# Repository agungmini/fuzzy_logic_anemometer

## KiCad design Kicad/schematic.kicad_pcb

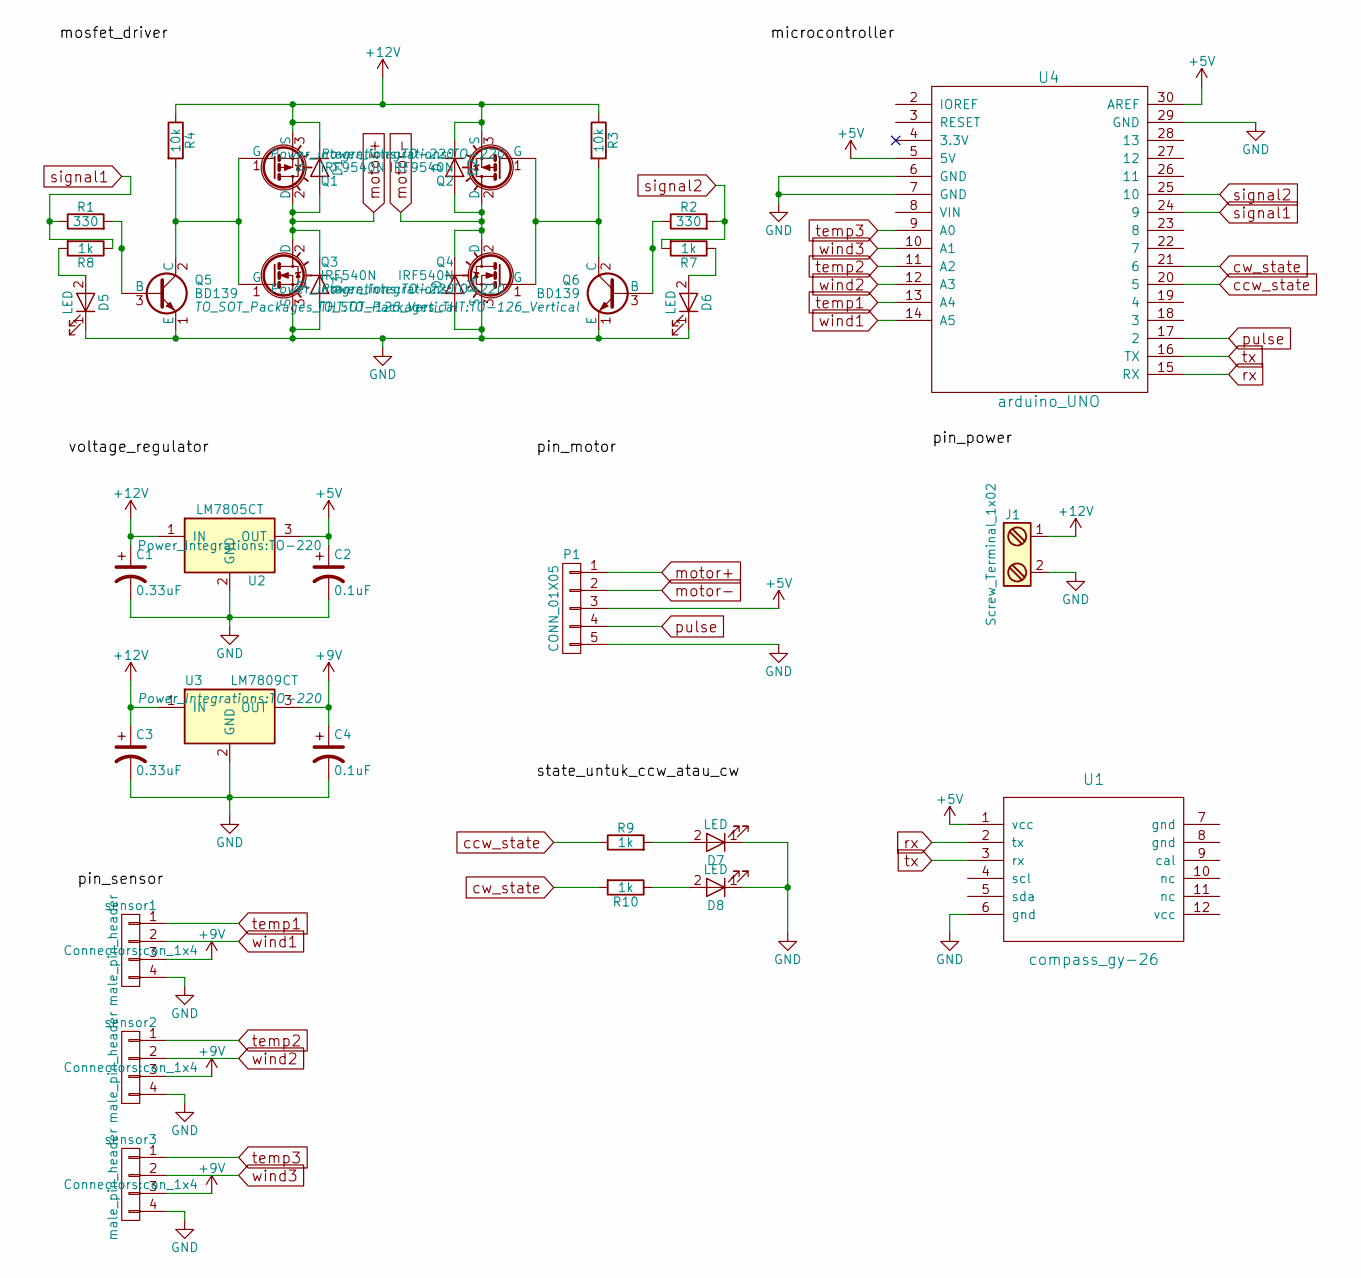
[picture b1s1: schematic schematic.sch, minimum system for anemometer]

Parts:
C1, C3: 0.33uF; CP_Radial_D5.0mm_P2.50mm
C2, C4: 0.1uF; CP_Radial_D5.0mm_P2.50mm
D1, D2, D3, D4: D; D_A-405_P10.16mm_Horizontal
D5, D6, D7, D8: LED; LED_D5.0mm
J1: Screw_Terminal_1x02; TerminalBlock_Phoenix_MKDS1.5-2pol
P1: CONN_01X05; JST_EH_B05B-EH-A_05x2.50mm_Straight
Q1, Q2: IRF9540N; TO-220
Q3, Q4: IRF540N; TO-220
Q5, Q6: BD139; TO-126_Vertical
R1, R2: 330; R_Axial_DIN0207_L6.3mm_D2.5mm_P10.16mm_Horizontal
R3, R4: 10k; R_Axial_DIN0207_L6.3mm_D2.5mm_P10.16mm_Horizontal
R7, R8, R9, R10: 1k; R_Axial_DIN0207_L6.3mm_D2.5mm_P10.16mm_Horizontal
U1: compass_gy-26
U2: LM7805CT; TO-220
U3: LM7809CT; TO-220
U4: arduino_UNO; arduino_uno
sensor1, sensor2, sensor3: male_pin_header; con_1x4

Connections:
+5V: C2.1, P1.3, U1.1 (vcc), U2.3 (OUT), U4.5 (5V), U4.30 (AREF)
+9V: C4.1, U3.3 (OUT), sensor1.3, sensor2.3, sensor3.3
+12V: C1.1, C3.1, D1.1 (K), D2.1 (K), J1.1, Q1.3 (S), Q2.3 (S), R3.1, R4.1, U2.1 (IN), U3.1 (IN)
GND: C1.2, C2.2, C3.2, C4.2, D3.2 (A), D4.2 (A), D5.1 (K), D6.1 (K), D7.1 (K), D8.1 (K), J1.2, P1.5, Q3.3 (S), Q4.3 (S), Q5.1 (E), Q6.1 (E), U1.6 (gnd), U2.2 (GND), U3.2 (GND), U4.6 (GND), U4.7 (GND), U4.29 (GND), sensor1.4, sensor2.4, sensor3.4
unnamed: D5.2 (A), R8.2
unnamed: D6.2 (A), R7.1
unnamed: D7.2 (A), R9.2
unnamed: D8.2 (A), R10.1
unnamed: Q1.1 (G), Q3.1 (G), Q5.2 (C), R4.2
unnamed: Q2.1 (G), Q4.1 (G), Q6.2 (C), R3.2
unnamed: Q5.3 (B), R1.2
unnamed: Q6.3 (B), R2.1
ccw_state: R9.1, U4.20 (5)
cw_state: R10.2, U4.21 (6)
motor+: D1.2 (A), D3.1 (K), P1.1, Q1.2 (D), Q3.2 (D)
motor-: D2.2 (A), D4.1 (K), P1.2, Q2.2 (D), Q4.2 (D)
pulse: P1.4, U4.17 (2)
rx: U1.2 (tx), U4.15 (RX)
signal1: R1.1, R8.1, U4.24 (9)
signal2: R2.2, R7.2, U4.25 (10)
temp1: U4.13 (A4), sensor1.1
temp2: U4.11 (A2), sensor2.1
temp3: U4.9 (A0), sensor3.1
tx: U1.3 (rx), U4.16 (TX)
wind1: U4.14 (A5), sensor1.2
wind2: U4.12 (A3), sensor2.2
wind3: U4.10 (A1), sensor3.2

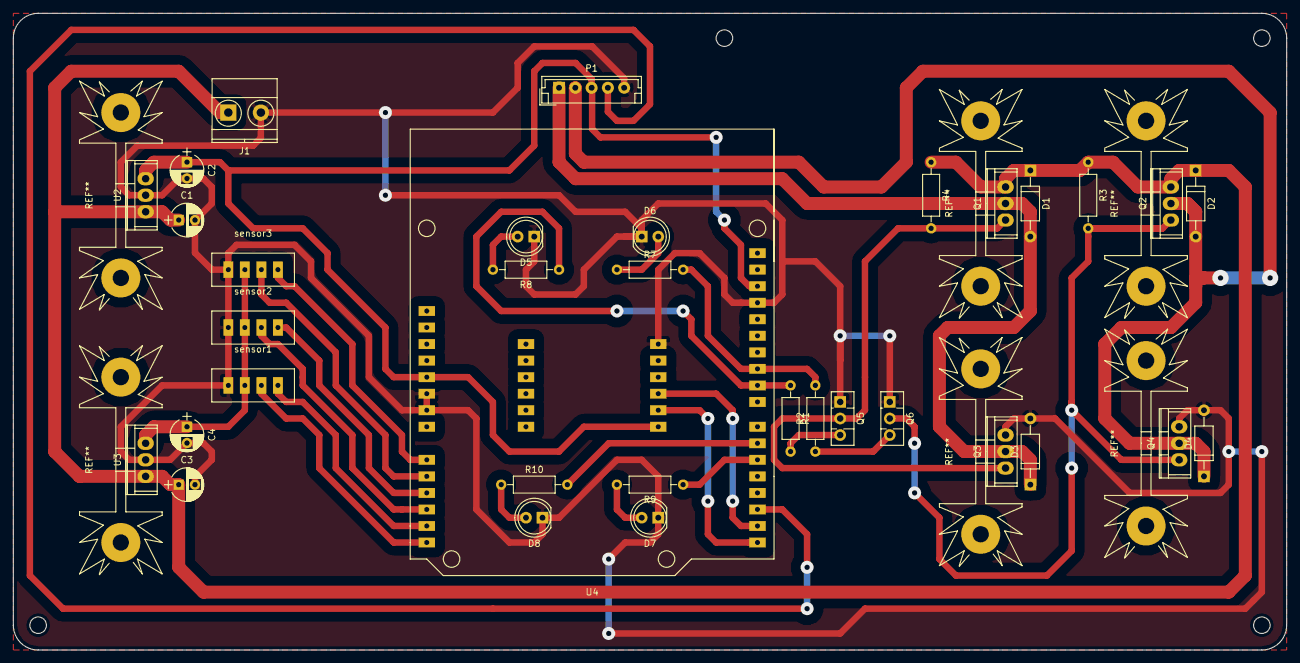
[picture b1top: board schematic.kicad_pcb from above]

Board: 2 copper layers, 195.6 x 97.8 mm, 35 parts (1 on the bottom side), 27 nets.
